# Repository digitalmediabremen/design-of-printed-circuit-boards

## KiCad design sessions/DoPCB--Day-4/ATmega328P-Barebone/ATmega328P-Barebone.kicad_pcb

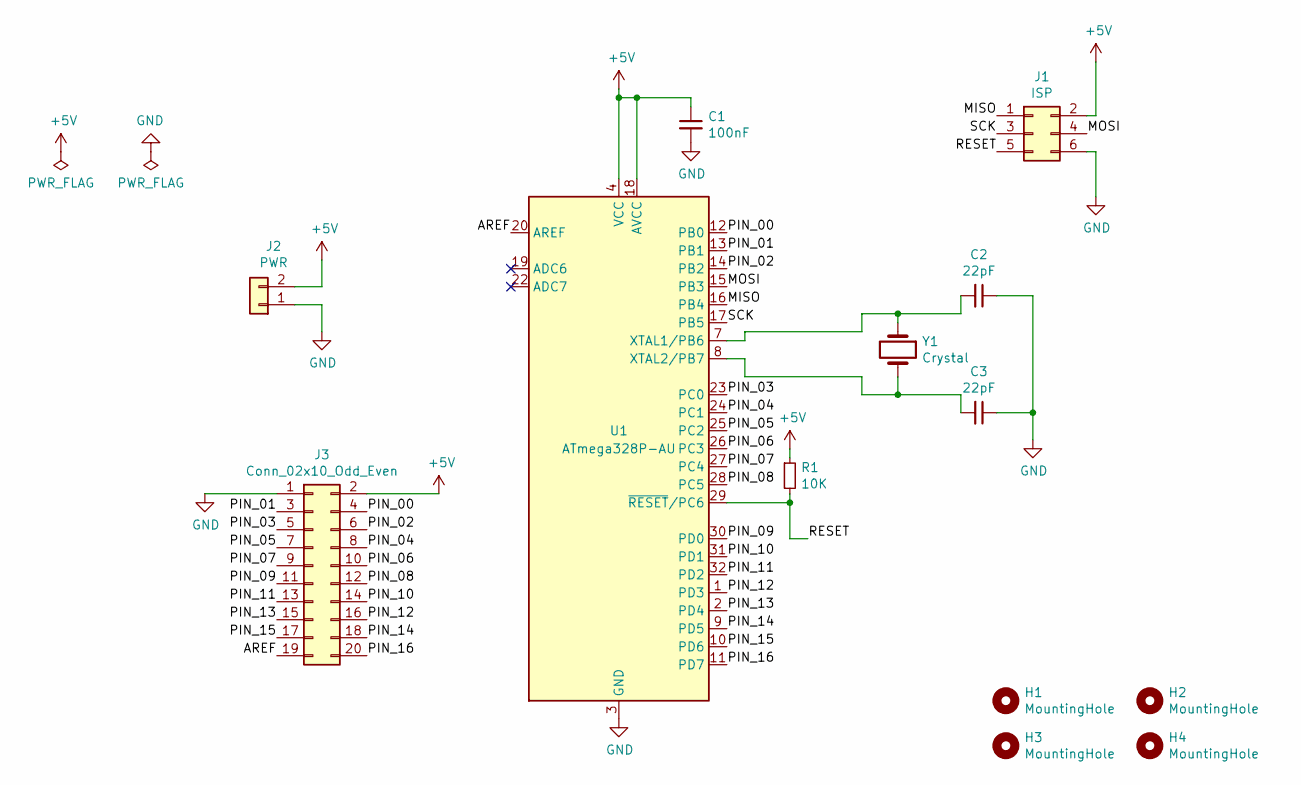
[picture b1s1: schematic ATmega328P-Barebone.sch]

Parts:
C1: 100nF; C_0805_2012Metric_Pad1.18x1.45mm_HandSolder; JLCPCB Part # C49678
C2, C3: 22pF; C_0805_2012Metric_Pad1.18x1.45mm_HandSolder; JLCPCB Part # C1804
H1, H2, H3, H4: MountingHole; MountingHole_3.2mm_M3
J1: ISP; PinHeader_2x03_P2.54mm_Vertical
J2: PWR; PinHeader_1x02_P2.54mm_Vertical
J3: Conn_02x10_Odd_Even; PinHeader_2x10_P2.54mm_Vertical
R1: 10K; R_0805_2012Metric_Pad1.20x1.40mm_HandSolder; JLCPCB Part # C17414
U1: ATmega328P-AU; TQFP-32_7x7mm_P0.8mm; JLCPCB Part # C14877
Y1: Crystal; Crystal_SMD_HC49-SD; JLCPCB Part # C12674

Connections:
+5V: C1.1, J1.2, J2.2, J3.2, R1.1, U1.4 (VCC), U1.6 (VCC), U1.18 (AVCC)
/AREF: J3.19, U1.20 (AREF)
/MISO: J1.1, U1.16 (PB4)
/MOSI: J1.4, U1.15 (PB3)
/PIN_00: J3.4, U1.12 (PB0)
/PIN_01: J3.3, U1.13 (PB1)
/PIN_02: J3.6, U1.14 (PB2)
/PIN_03: J3.5, U1.23 (PC0)
/PIN_04: J3.8, U1.24 (PC1)
/PIN_05: J3.7, U1.25 (PC2)
/PIN_06: J3.10, U1.26 (PC3)
/PIN_07: J3.9, U1.27 (PC4)
/PIN_08: J3.12, U1.28 (PC5)
/PIN_09: J3.11, U1.30 (PD0)
/PIN_10: J3.14, U1.31 (PD1)
/PIN_11: J3.13, U1.32 (PD2)
/PIN_12: J3.16, U1.1 (PD3)
/PIN_13: J3.15, U1.2 (PD4)
/PIN_14: J3.18, U1.9 (PD5)
/PIN_15: J3.17, U1.10 (PD6)
/PIN_16: J3.20, U1.11 (PD7)
/RESET: J1.5, R1.2, U1.29 (~RESET~/PC6)
/SCK: J1.3, U1.17 (PB5)
GND: C1.2, C2.1, C3.1, J1.6, J2.1, J3.1, U1.3 (GND), U1.5 (GND), U1.21 (GND)
unnamed: C2.2, U1.7 (XTAL1/PB6), Y1.1
unnamed: C3.2, U1.8 (XTAL2/PB7), Y1.2

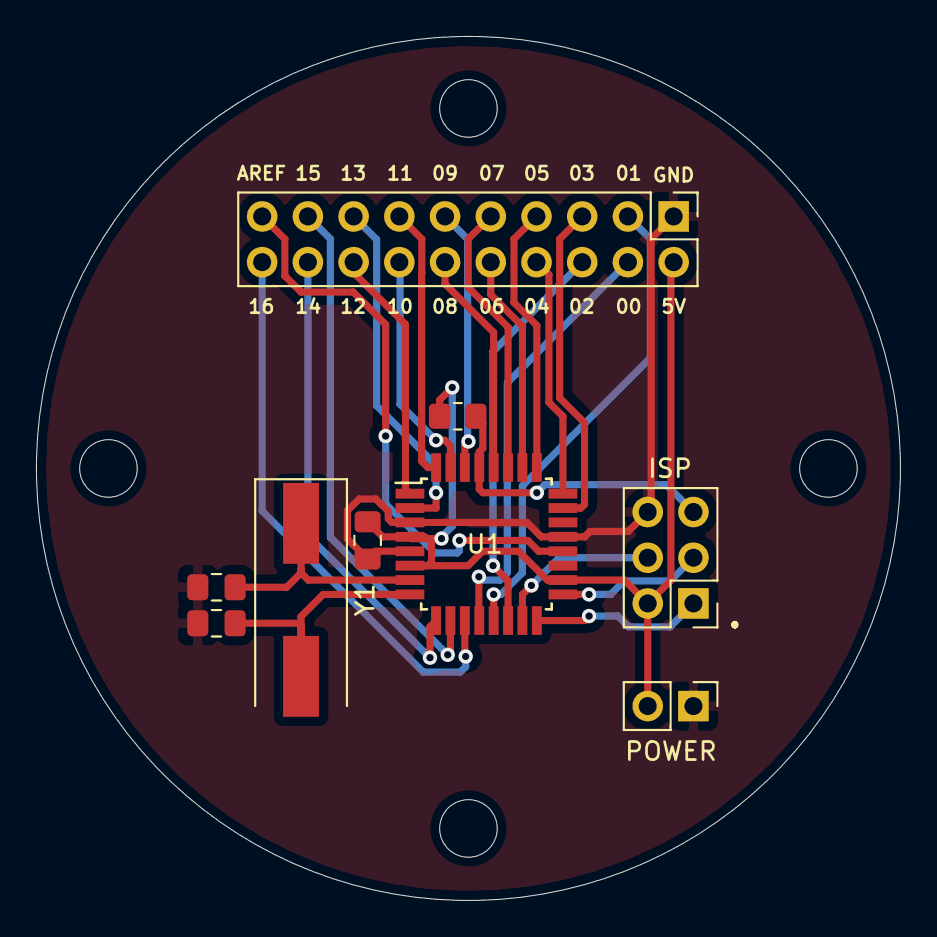
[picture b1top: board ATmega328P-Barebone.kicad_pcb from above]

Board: 2 copper layers, 48.0 x 48.0 mm, 13 parts (0 on the bottom side), 26 nets.

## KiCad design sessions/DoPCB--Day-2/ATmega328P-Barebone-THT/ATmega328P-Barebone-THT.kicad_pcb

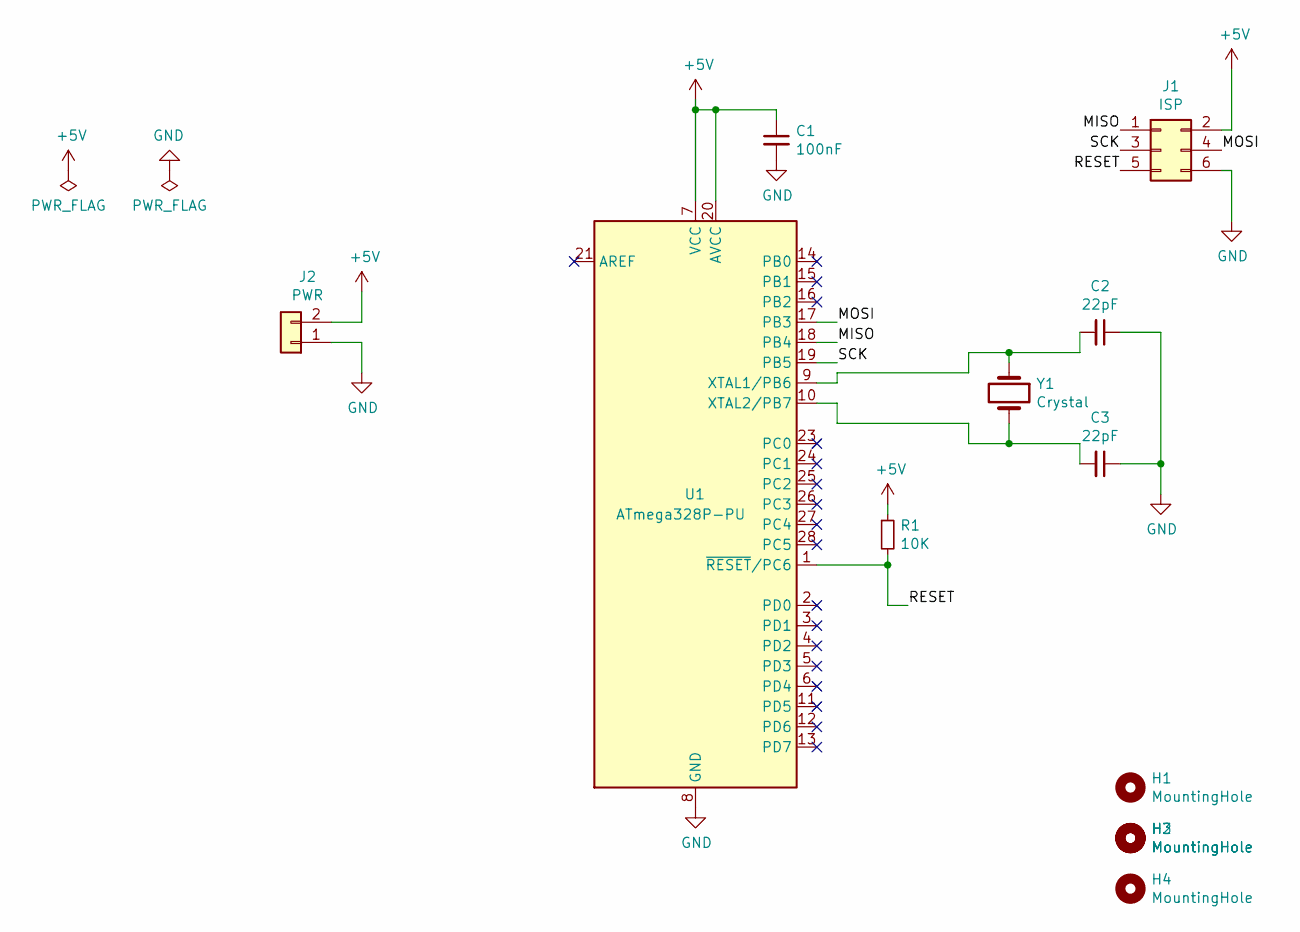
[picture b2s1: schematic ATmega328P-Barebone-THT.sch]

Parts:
C1: 100nF; C_Radial_D6.3mm_H5.0mm_P2.50mm
C2, C3: 22pF; C_Radial_D10.0mm_H12.5mm_P5.00mm
H1, H2, H3, H4: MountingHole; MountingHole_3.2mm_M3
J1: ISP; PinSocket_2x03_P2.54mm_Vertical
J2: PWR; PinHeader_1x02_P2.54mm_Vertical
R1: 10K; R_Axial_DIN0207_L6.3mm_D2.5mm_P10.16mm_Horizontal
U1: ATmega328P-PU; DIP-28_W7.62mm_Socket
Y1: Crystal; Crystal_HC49-U_Vertical

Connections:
+5V: C1.1, J1.2, J2.2, R1.1, U1.7 (VCC), U1.20 (AVCC)
/MISO: J1.1, U1.18 (PB4)
/MOSI: J1.4, U1.17 (PB3)
/RESET: J1.5, R1.2, U1.1 (~RESET~/PC6)
/SCK: J1.3, U1.19 (PB5)
GND: C1.2, C2.1, C3.1, J1.6, J2.1, U1.8 (GND), U1.22 (GND)
unnamed: C2.2, U1.9 (XTAL1/PB6), Y1.1
unnamed: C3.2, U1.10 (XTAL2/PB7), Y1.2

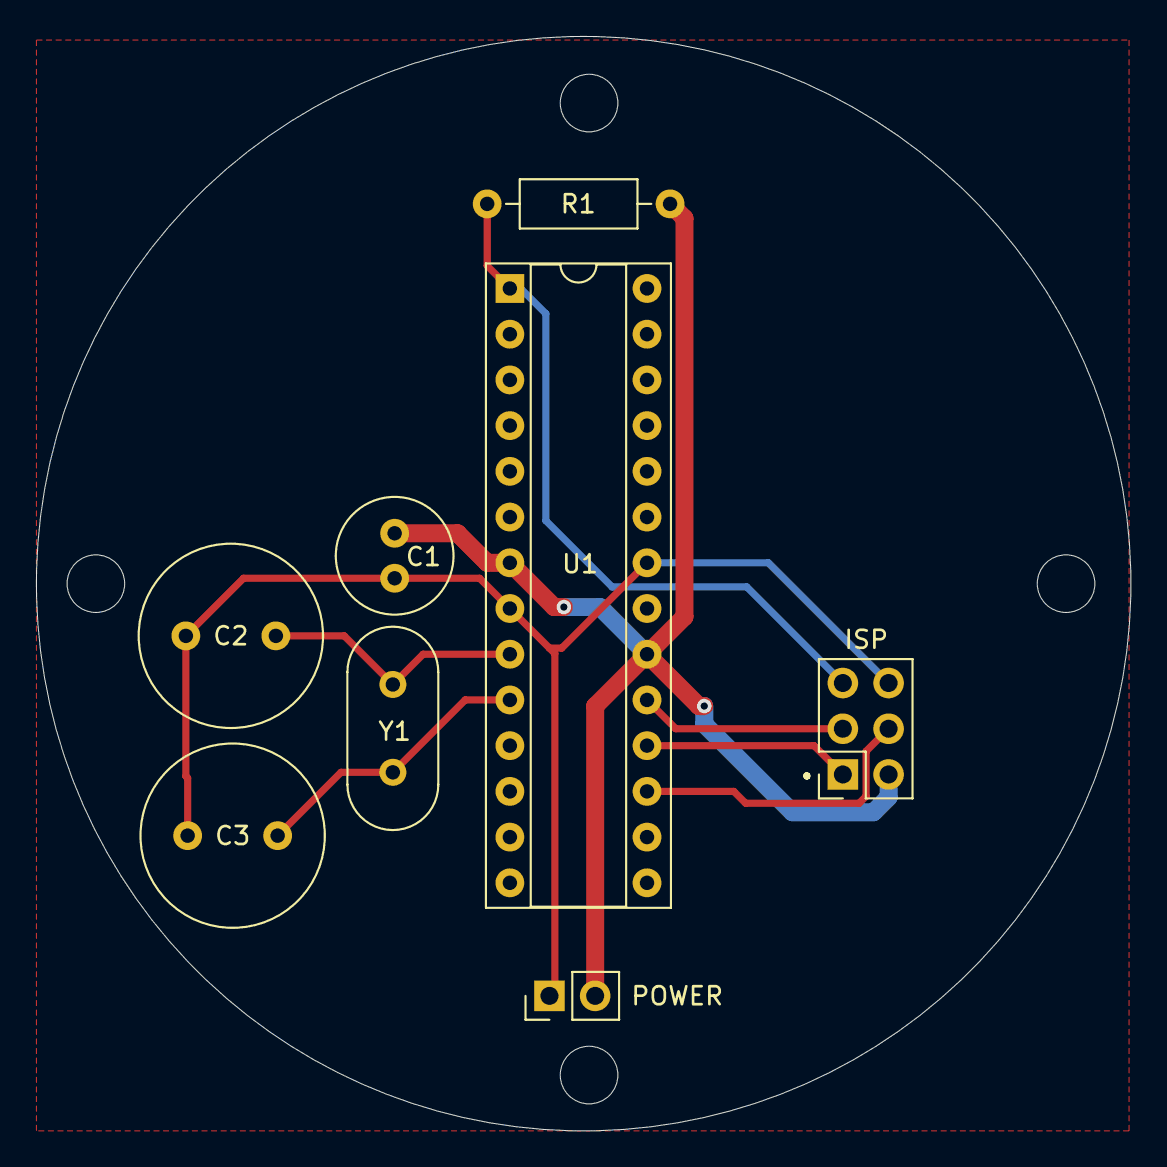
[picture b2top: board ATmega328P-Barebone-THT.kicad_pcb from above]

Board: 2 copper layers, 60.8 x 60.8 mm, 12 parts (0 on the bottom side), 8 nets.

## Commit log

2021-10-05 added ATmega328P BareBone
2021-10-05 added gitignore
2021-10-06 updated day-2, added day-3
2021-10-07 renamed keywords to glossary
2021-10-07 updated day 4
2021-10-07 added final ATmega328P design in day 4
2021-10-08 updated day 2 with custom components
2021-10-08 added day 5
2021-10-08 added project proposals
2021-10-08 added HUI
